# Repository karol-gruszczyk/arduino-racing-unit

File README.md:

# Racing Unit
Launch Control, Wheelie Control, QuickShifter

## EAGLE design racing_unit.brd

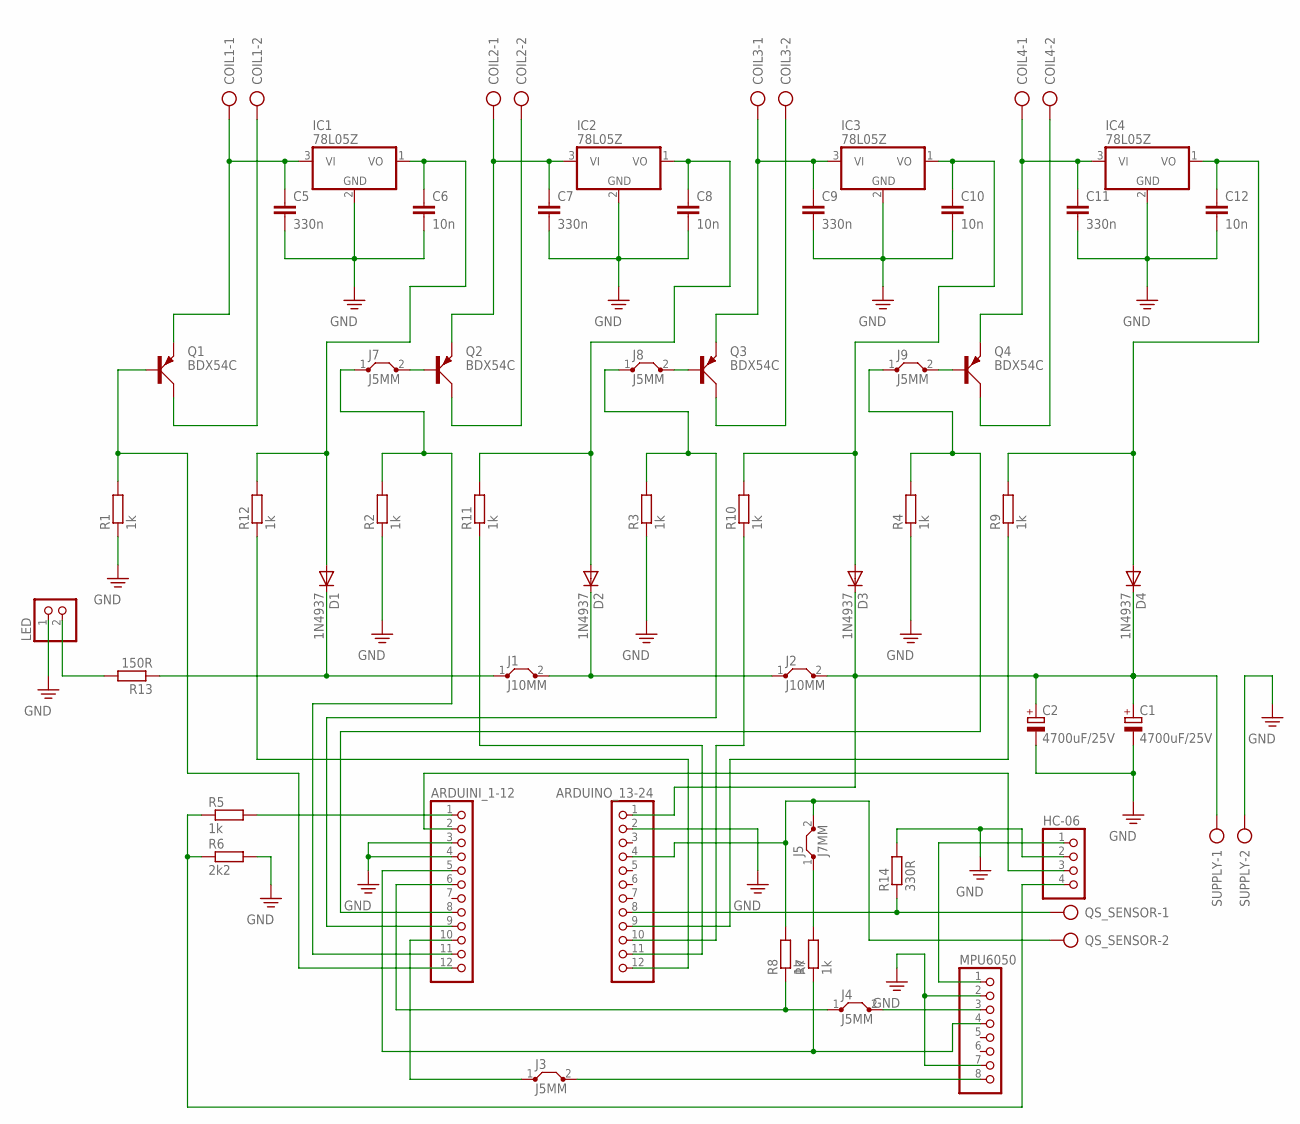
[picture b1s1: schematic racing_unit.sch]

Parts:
ARDUINI_1-12: PINHD-1X12; 1X12
ARDUINO_13-24: PINHD-1X12; 1X12
C1, C2: 4700uF/25V; E7,5-16
C5, C7, C9, C11: 330n; C050-024X044
C6, C8, C10, C12: 10n; C050-024X044
COIL1, COIL2, COIL3, COIL4: AK500/2
D1, D2, D3, D4: 1N4937; DO41-10
HC-06: PINHD-1X4; 1X04
IC1, IC2, IC3, IC4: 78L05Z; TO92
J1, J2: J10MM; 10
J3, J4, J7, J8, J9: J5MM; 05
J5: J7MM; 07
LED: PINHD-1X2; 1X02
MPU6050: PINHD-1X8; 1X08
Q1, Q2, Q3, Q4: BDX54C; TO220AV
QS_SENSOR: AK500/2
R1, R2, R3, R4, R5, R7, R8, R9, R10, R11, R12: 1k; 0204/5
R6: 2k2; 0204/5
R13: 150R; 0204/5
R14: 330R; 0204/5
SUPPLY: AK500/2

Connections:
GND: ARDUINI_1-12.3, ARDUINI_1-12.4, ARDUINO_13-24.2, C1.-, C2.-, C5.2, C6.2, C7.2, C8.2, C9.2, C10.2, C11.2, C12.2, HC-06.2, IC1.2 (GND), IC2.2 (GND), IC3.2 (GND), IC4.2 (GND), LED.1, MPU6050.2, MPU6050.7, R1.1, R2.1, R3.1, R4.1, R6.2, R14.2, SUPPLY.2
unnamed: C5.1, COIL1.1, IC1.3 (VI), Q1.E
unnamed: C7.1, COIL2.1, IC2.3 (VI), Q2.E
unnamed: C9.1, COIL3.1, IC3.3 (VI), Q3.E
unnamed: C11.1, COIL4.1, IC4.3 (VI), Q4.E
unnamed: ARDUINI_1-12.2, HC-06.3
unnamed: D1.C, J1.1, R13.1
unnamed: D2.C, J1.2, J2.1
unnamed: COIL4.2, Q4.C
unnamed: COIL3.2, Q3.C
unnamed: COIL2.2, Q2.C
unnamed: COIL1.2, Q1.C
unnamed: LED.2, R13.2
unnamed: C6.1, D1.A, IC1.1 (VO), R12.2
unnamed: C8.1, D2.A, IC2.1 (VO), R11.2
unnamed: ARDUINO_13-24.8, QS_SENSOR.1, R14.1
unnamed: C12.1, D4.A, IC4.1 (VO), R9.2
unnamed: ARDUINO_13-24.4, J5.2, QS_SENSOR.2, R8.2
unnamed: ARDUINO_13-24.1, C1.+, C2.+, D3.C, D4.C, J2.2, SUPPLY.1
unnamed: ARDUINI_1-12.10, J3.1
unnamed: C10.1, D3.A, IC3.1 (VO), R10.2
unnamed: ARDUINI_1-12.1, R5.2
unnamed: ARDUINO_13-24.12, R12.1
unnamed: ARDUINO_13-24.11, R11.1
unnamed: ARDUINO_13-24.10, R10.1
unnamed: ARDUINO_13-24.9, R9.1
unnamed: ARDUINI_1-12.6, J4.1, R8.1
unnamed: ARDUINI_1-12.12, Q1.B, R1.2
unnamed: J3.2, MPU6050.8
unnamed: J7.2, Q2.B
unnamed: ARDUINI_1-12.5, MPU6050.4, R7.1
unnamed: HC-06.4, R5.1, R6.1
unnamed: J4.2, MPU6050.3
unnamed: HC-06.1, MPU6050.1
unnamed: ARDUINI_1-12.11, J7.1, R2.2
unnamed: J5.1, R7.2
unnamed: J8.2, Q3.B
unnamed: ARDUINI_1-12.9, J8.1, R3.2
unnamed: J9.2, Q4.B
unnamed: ARDUINI_1-12.8, J9.1, R4.2

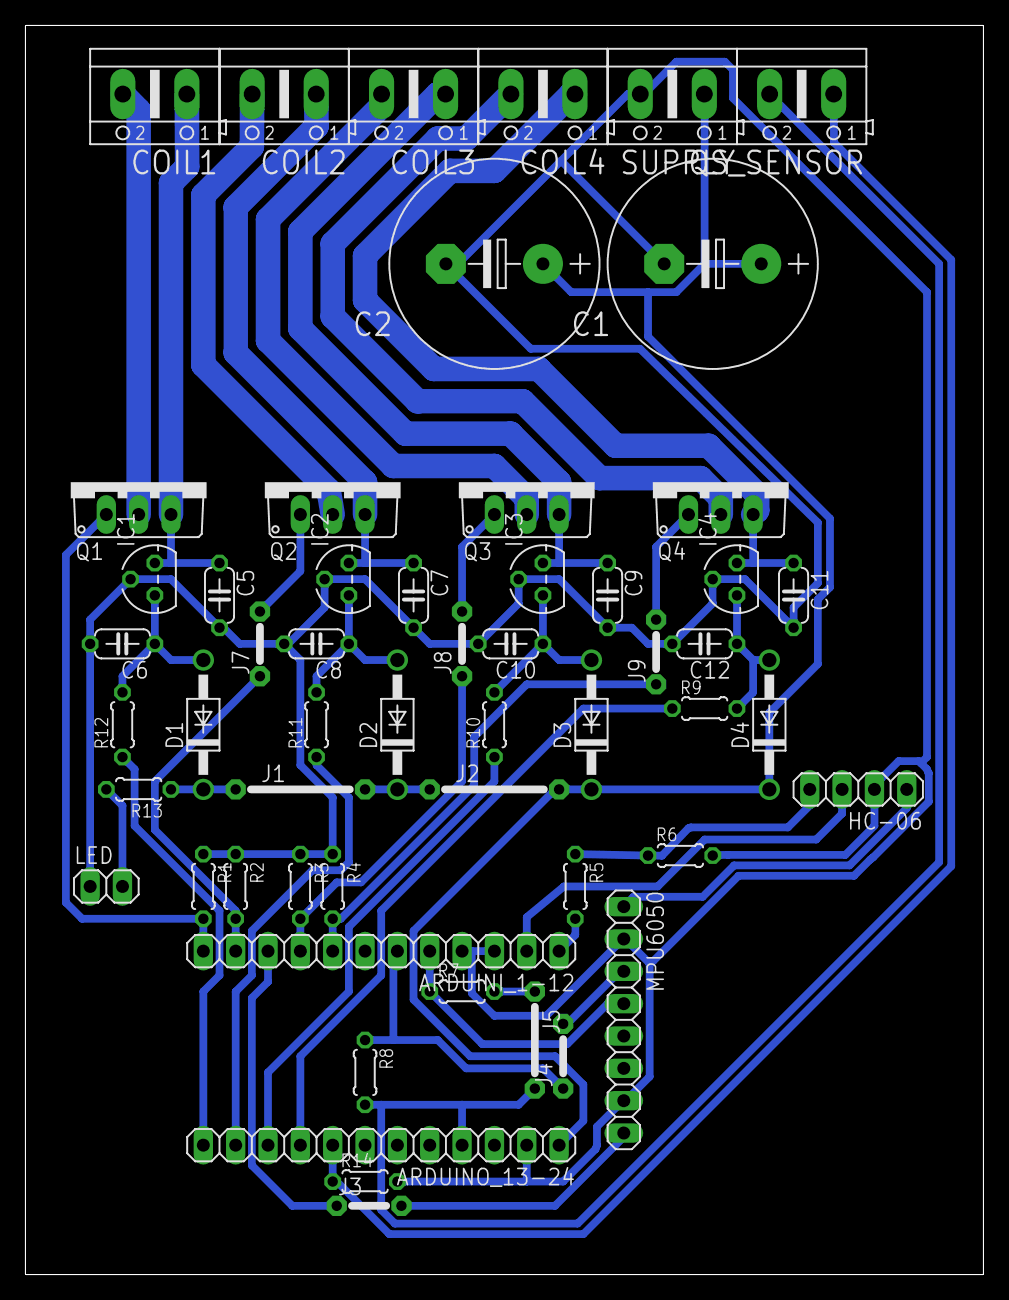
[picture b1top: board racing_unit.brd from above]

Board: 2 copper layers, 75.2 x 98.1 mm, 55 parts (0 on the bottom side), 40 nets.

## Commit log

2016-08-11 initial
2016-08-11 added launch control enabling
2016-08-12 fixed rpm measurement
2016-08-13 added schematic
2016-08-14 added interrupts for every cylinder and optymized types
2016-08-18 changed interrupts to change pin interrupts
2016-08-22 added setup project
2016-08-23 added eeprom settings and bluetooth connection
2016-08-24 changed coil killing procedure
2016-08-29 added anrdroid controller app
2016-08-29 changed settings activity for better UX
2016-08-29 improved screen_on on main screen activity
2016-08-29 improved bt context and added spark cut-off test
2016-08-30 fixed lights switch and improved bt sockets
2016-08-30 added quickshifter sensor reading
2016-08-30 improved voltage divider calculation
2016-08-30 fixed kill times
2016-08-31 updated schematic
2016-08-31 fixed interrupts
2016-08-31 changed quick shifter vars
2016-08-31 fixed initial pcint values
2016-09-03 reorganized code and seperated coils module
2016-09-05 added pcb design
2016-09-05 fixed pcb
2016-09-06 updated pcb and schematic
2016-09-08 updated pcb and improved spark killing procedure
2016-09-13 changed design to SMD
2016-09-13 removed caption in schematic
2016-09-13 changed code to match arduino uno / atmega328p
2016-09-13 improved BT and MPU module
2016-09-14 improved schematic
2016-09-14 changed coil switches to mosfet's
2016-09-15 added mosfet drivers and refactored launch control to be started by first spark kill
2016-09-18 improved rpm measurement
2016-09-19 updated android app icon
2016-09-20 fixed code warnings
2016-09-20 added eagle files do .gitignore
2017-01-27 removed +12v supply from coils
